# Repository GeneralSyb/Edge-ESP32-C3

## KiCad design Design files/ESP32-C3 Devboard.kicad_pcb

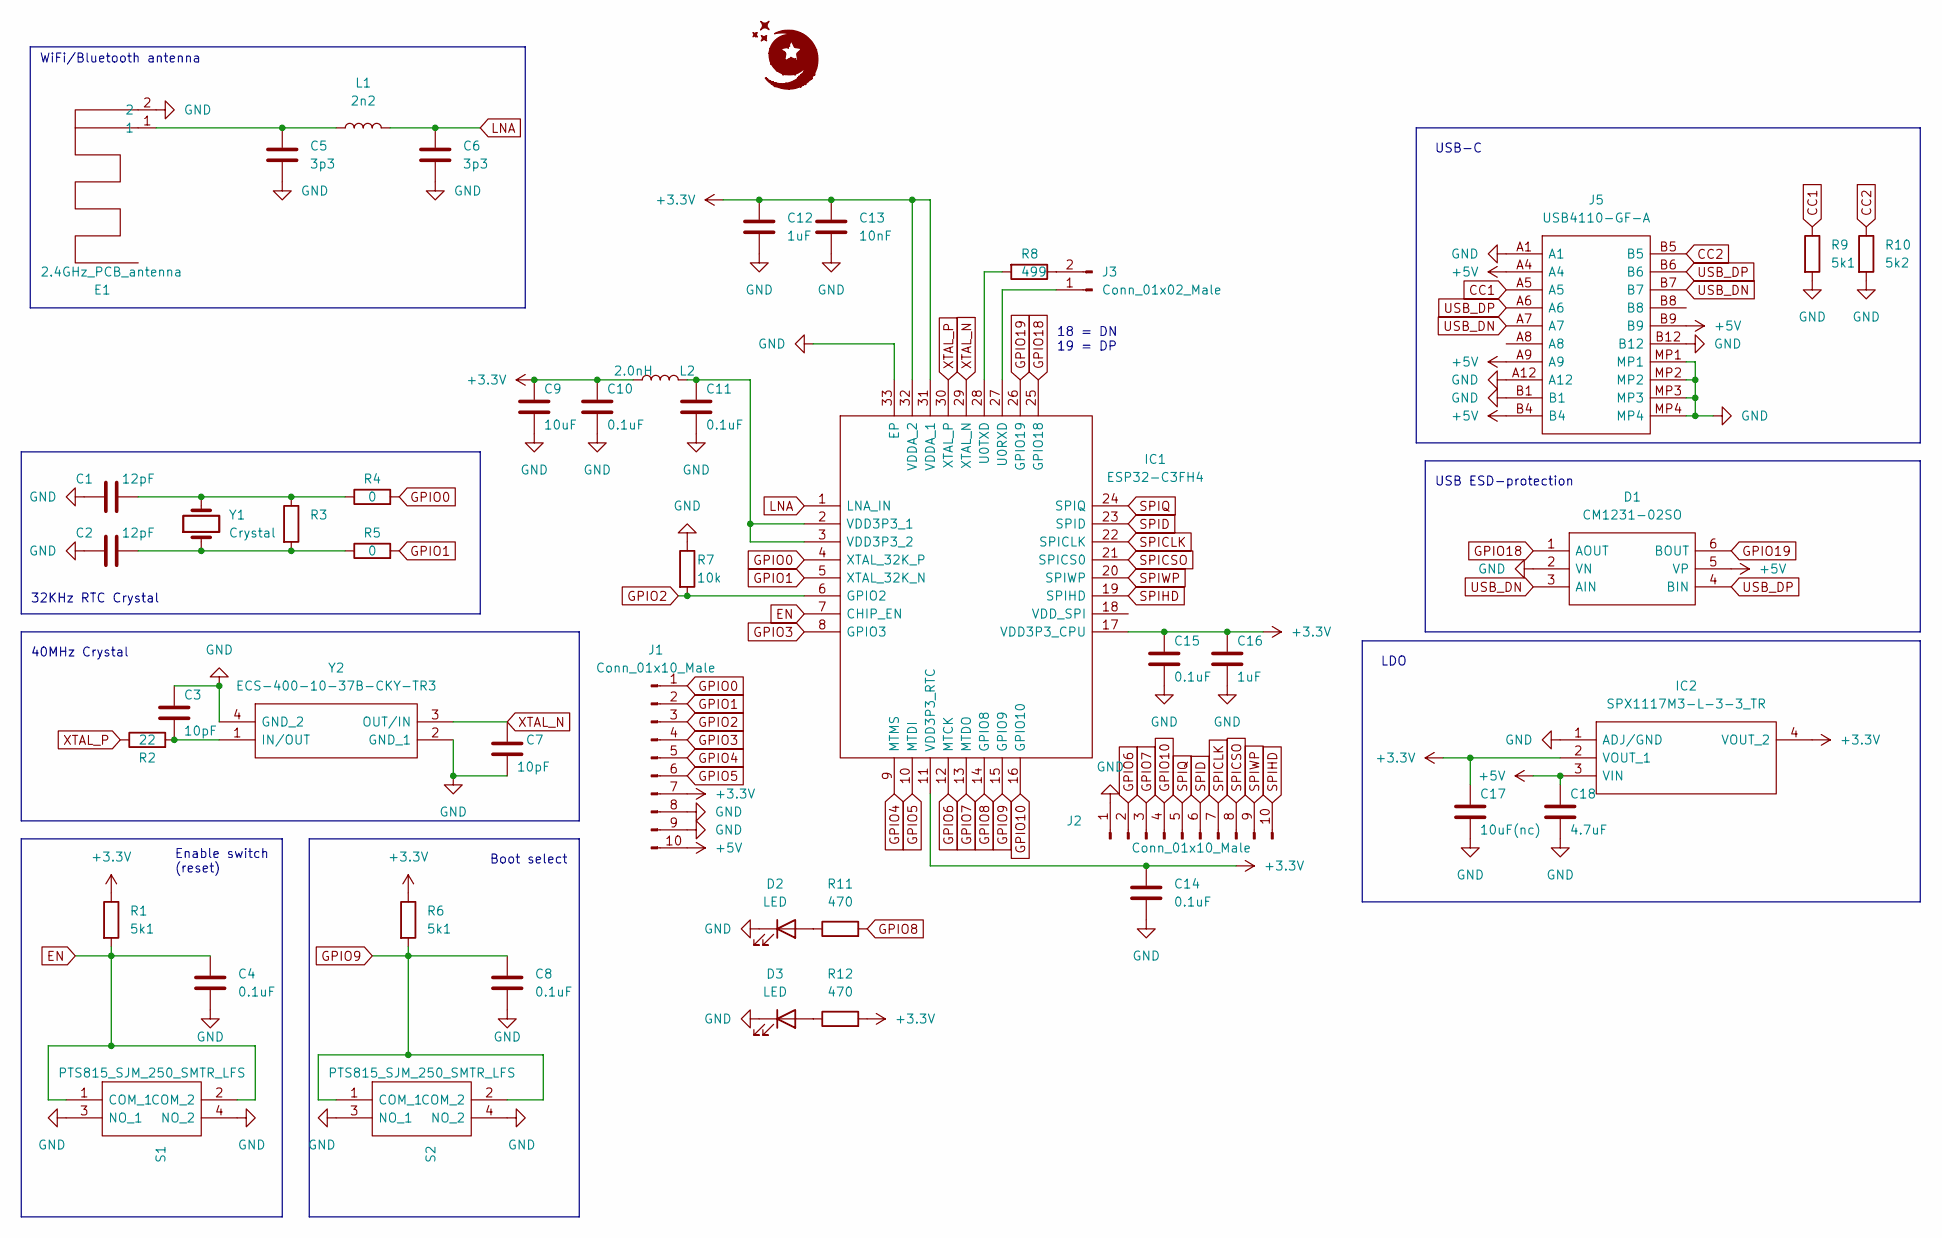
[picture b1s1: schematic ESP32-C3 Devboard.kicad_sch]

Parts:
C1, C2: 12pF; C_0402_1005Metric
C3, C7: 10pF; C_0402_1005Metric
C4, C8, C10, C11, C14, C15: 0.1uF; C_0402_1005Metric
C5, C6: 3p3; C_0402_1005Metric
C9: 10uF; C_0402_1005Metric
C12, C16: 1uF; C_0402_1005Metric
C13: 10nF; C_0402_1005Metric
C17: 10uF(nc); C_0402_1005Metric
C18: 4.7uF; C_0402_1005Metric
D1: CM1231-02SO; SOT95P280X145-6N; Mouser Part Number 748-CM1231-02SO
D2, D3: LED; LED_0603_1608Metric
E1: 2.4GHz_PCB_antenna; Texas_SWRA117D_2.4GHz_Right
IC1: ESP32-C3FH4; Mouser Part Number 356-ESP32-C3FH4
IC2: SPX1117M3-L-3-3_TR; SOT230P700X180-4N; Mouser Part Number 701-SPX1117M3-L-33TR
J1, J2: Conn_01x10_Male; PinHeader_1x10_P2.54mm_Vertical
J3: Conn_01x02_Male; PinHeader_1x02_P2.54mm_Vertical
J5: USB4110-GF-A; USB4110GFA; Mouser Part Number 640-USB4110-GF-A
L1: 2n2; L_0402_1005Metric
L2: 2.0nH; L_0402_1005Metric
R1, R6, R9: 5k1; R_0402_1005Metric
R2: 22; R_0402_1005Metric
R3: R_0402_1005Metric
R4, R5: 0; R_0402_1005Metric
R7: 10k; R_0402_1005Metric
R8: 499; R_0402_1005Metric
R10: 5k2; R_0402_1005Metric
R11, R12: 470; R_0402_1005Metric
S1, S2: PTS815_SJM_250_SMTR_LFS; PTS815SJM250SMTRLFS; Mouser Part Number 611-PTS815SJM250SMTR
Y1: Crystal; Crystal_C26-LF_D2.1mm_L6.5mm_Horizontal
Y2: ECS-400-10-37B-CKY-TR3; ECS4001037BCKYTR3; Mouser Part Number 520-EC4001037BCKYTR3

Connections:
+3.3V: C9.1, C10.1, C12.1, C13.1, C14.1, C15.1, C16.1, C17.1, IC1.11 (VDD3P3_RTC), IC1.17 (VDD3P3_CPU), IC1.31 (VDDA_1), IC1.32 (VDDA_2), IC2.2 (VOUT_1), IC2.4 (VOUT_2), J1.7, L2.1, R1.1, R6.1, R12.2
+5V: C18.1, D1.5 (VP), IC2.3 (VIN), J1.10, J5.A4, J5.A9, J5.B4, J5.B9
CC1: J5.A5, R9.1
CC2: J5.B5, R10.1
EN: C4.1, IC1.7 (CHIP_EN), R1.2, S1.1 (COM_1), S1.2 (COM_2)
GND: C1.1, C2.1, C3.1, C4.2, C5.2, C6.2, C7.2, C8.2, C9.2, C10.2, C11.2, C12.2, C13.2, C14.2, C15.2, C16.2, C17.2, C18.2, D1.2 (VN), D2.1 (K), D3.1 (K), E1.2, IC1.33 (EP), IC2.1 (ADJ/GND), J1.8, J1.9, J2.1, J5.A1, J5.A12, J5.B1, J5.B12, J5.MP1, J5.MP2, J5.MP3, J5.MP4, R7.1, R9.2, R10.2, S1.3 (NO_1), S1.4 (NO_2), S2.3 (NO_1), S2.4 (NO_2), Y2.2 (GND_1), Y2.4 (GND_2)
GPIO0: IC1.4 (XTAL_32K_P), J1.1, R4.2
GPIO1: IC1.5 (XTAL_32K_N), J1.2, R5.2
GPIO2: IC1.6 (GPIO2), J1.3, R7.2
GPIO3: IC1.8 (GPIO3), J1.4
GPIO4: IC1.9 (MTMS), J1.5
GPIO5: IC1.10 (MTDI), J1.6
GPIO6: IC1.12 (MTCK), J2.2
GPIO7: IC1.13 (MTDO), J2.3
GPIO8: IC1.14 (GPIO8), R11.2
GPIO9: C8.1, IC1.15 (GPIO9), R6.2, S2.1 (COM_1), S2.2 (COM_2)
GPIO10: IC1.16 (GPIO10), J2.4
GPIO18: D1.1 (AOUT), IC1.25 (GPIO18)
GPIO19: D1.6 (BOUT), IC1.26 (GPIO19)
LNA: C6.1, IC1.1 (LNA_IN), L1.2
unnamed: C1.2, R3.1, R4.1, Y1.2
unnamed: C2.2, R3.2, R5.1, Y1.1
unnamed: C3.2, R2.2, Y2.1 (IN/OUT)
unnamed: C5.1, E1.1, L1.1
unnamed: C11.1, IC1.2 (VDD3P3_1), IC1.3 (VDD3P3_2), L2.2
unnamed: D2.2 (A), R11.1
unnamed: D3.2 (A), R12.1
unnamed: IC1.27 (U0RXD), J3.1
unnamed: IC1.28 (U0TXD), R8.2
unnamed: J3.2, R8.1
SPICLK: IC1.22 (SPICLK), J2.7
SPICSO: IC1.21 (SPICS0), J2.8
SPID: IC1.23 (SPID), J2.6
SPIHD: IC1.19 (SPIHD), J2.10
SPIQ: IC1.24 (SPIQ), J2.5
SPIWP: IC1.20 (SPIWP), J2.9
USB_DN: D1.3 (AIN), J5.A7, J5.B7
USB_DP: D1.4 (BIN), J5.A6, J5.B6
XTAL_N: C7.1, IC1.29 (XTAL_N), Y2.3 (OUT/IN)
XTAL_P: IC1.30 (XTAL_P), R2.1

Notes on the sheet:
LDO
32KHz RTC Crystal
USB-C
Enable switch (reset)
40MHz Crystal
18 = DN 19 = DP
Boot select
USB ESD-protection
WiFi/Bluetooth antenna

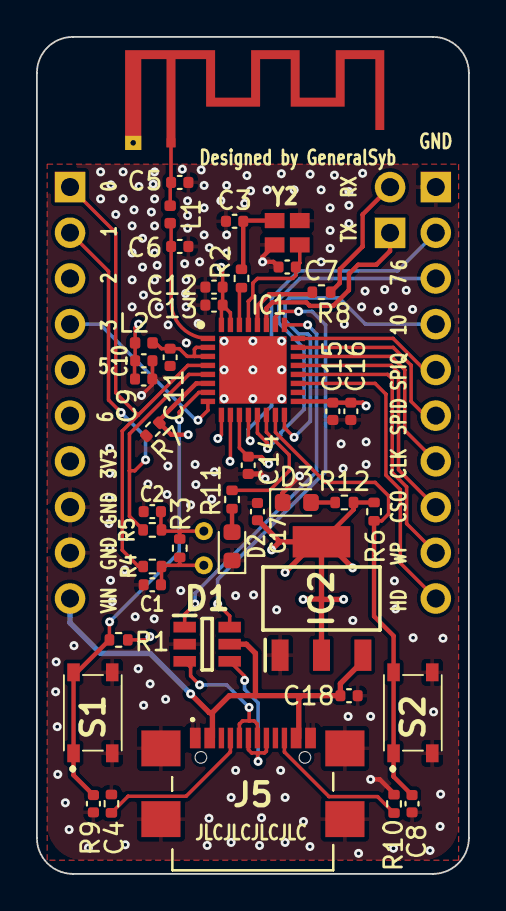
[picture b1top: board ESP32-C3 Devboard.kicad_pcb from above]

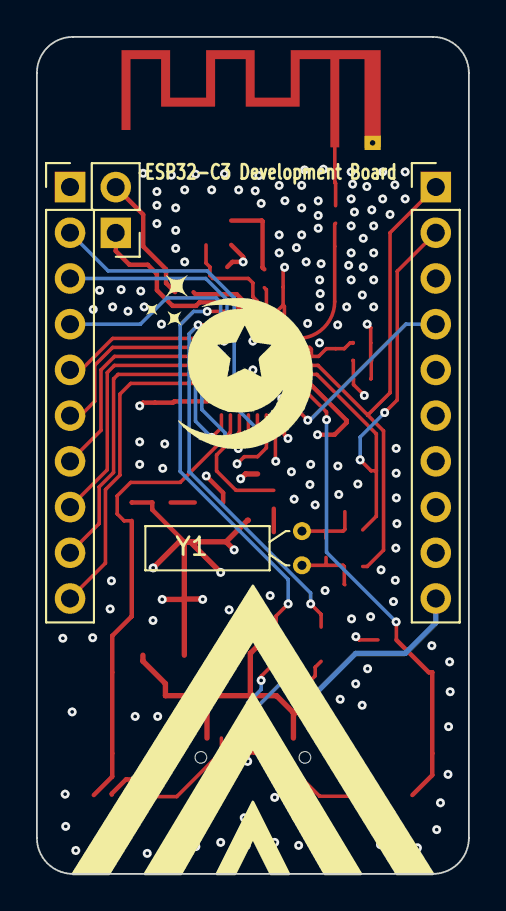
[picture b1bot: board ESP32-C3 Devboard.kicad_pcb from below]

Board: 4 copper layers, 24.0 x 46.5 mm, 46 parts (4 on the bottom side), 40 nets.

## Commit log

2023-03-16 Pre-production v1
